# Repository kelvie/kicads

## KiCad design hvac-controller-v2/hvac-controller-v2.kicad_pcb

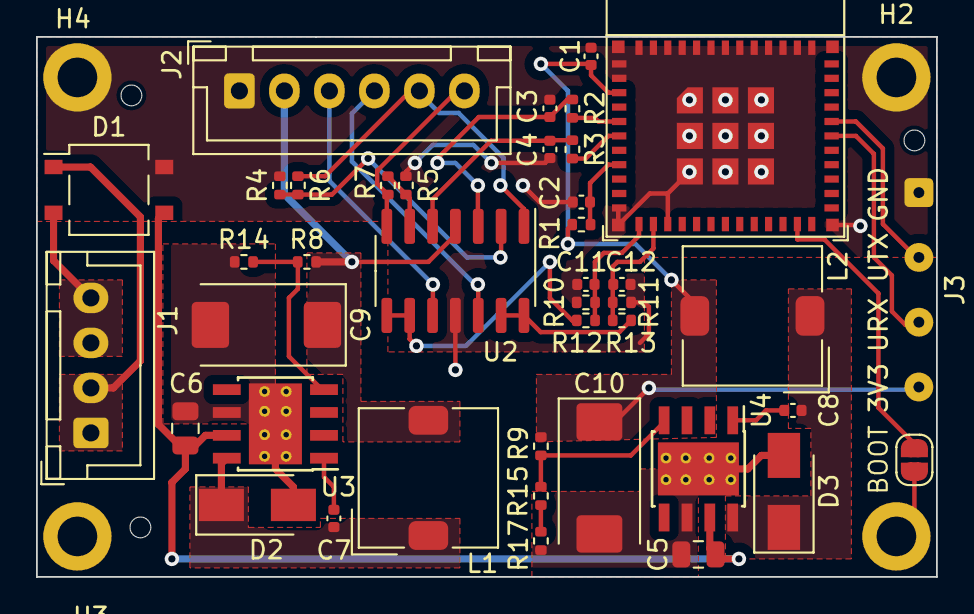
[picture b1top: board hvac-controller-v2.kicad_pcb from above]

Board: 2 copper layers, 50.0 x 30.0 mm, 48 parts (0 on the bottom side), 31 nets.

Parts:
C1: 0.01uF/16V; C_0402_1005Metric
C2, C3, C4: 1uF/5V; C_0402_1005Metric
C5, C6: 10uF/50V; C_0805_2012Metric
C7, C8: 0.01uF; C_0402_1005Metric
C9: 100uF/16V; CP_EIA-7343-31_Kemet-D
C10: 470uF/6.3V; CP_EIA-7343-31_Kemet-D
C11, C12: 0.1uF/16V; C_0402_1005Metric
D1: MB10S; TO-269AA
D2, D3: SS34; D_SMA
H1, H2, H3, H4: Hole; MountingHole_2.2mm_M2_DIN965_Pad
H5, H6, H7: ToolingHole; ToolingHole_1.152mm
J1: VAC IN; JST_XH_B4B-XH-A_1x04_P2.50mm_Vertical
J2: Conn_01x06; JST_XH_B6B-XH-A_1x06_P2.50mm_Vertical
J3: UART; SolderWire-0.1sqmm_1x04_P3.6mm_D0.4mm_OD1mm
JP1: BOOT; SolderJumper-2_P1.3mm_Open_RoundedPad1.0x1.5mm
L1, L2: 22uH; L_SXN_SMRH74-220MT
R1, R8, R9: 10k; R_0402_1005Metric
R2, R3, R14: 1.1k; R_0402_1005Metric
R4, R5: 33k; R_0402_1005Metric
R6, R7: 68k; R_0402_1005Metric
R10, R11: 18k; R_0402_1005Metric
R12, R13: 2k; R_0402_1005Metric
R15: 5.6k; R_0402_1005Metric
R17: 270; R_0402_1005Metric
U1: ESP32-C3-MINI-1
U2: LM324DT; SOIC-14_3.9x8.7mm_P1.27mm
U3, U4: TPS5430DDA; TI_SO-PowerPAD-8_ThermalVias

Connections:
+3V3: C1.1, C10.1, J3.4, L2.2, R1.1, R9.1, U1.3 (3V3)
+12V: C9.1, J2.2, L1.2, R8.1, U2.4 (V+)
+24VA: D1.2, J1.3, J1.4
-24VA: D1.1, J1.1, J1.2
/ADC1: C11.2, R10.2, R12.1, U1.12 (GPIO0/ADC1_CH0/XTAL_32K_P)
/ADC2: C12.2, R11.2, R13.1, U1.13 (GPIO1/ADC1_CH1/XTAL_32K_N)
/CTRL1_IN: J2.3, U2.10 (+)
/CTRL1_OUT: J2.5, R6.2, U2.1
/CTRL2_IN: J2.4, U2.12 (+)
/CTRL2_OUT: J2.6, R7.2, U2.7
/PH12: C7.2, D2.1 (K), L1.1, U3.8 (PH)
/PH33: C8.2, D3.1 (K), L2.1, U4.8 (PH)
/PWM1: R2.2, U1.5 (GPIO2/ADC1_CH2)
/PWM2: R3.2, U1.6 (GPIO3/ADC1_CH3)
/UART_RX: J3.3, U1.30 (GPIO20/U0RXD)
/UART_TX: J3.2, U1.31 (GPIO21/U0TXD)
GND: C1.2, C2.2, C3.2, C4.2, C5.2, C6.2, C9.2, C10.2, C11.1, C12.1, D1.4 (-), D2.2 (A), D3.2 (A), H1.1, H2.1, H3.1, H4.1, J2.1, J3.1, JP1.2 (B), R4.2, R5.2, R12.2, R13.2, R14.1, R17.1, U1.1 (GND), U1.2 (GND), U1.11 (GND), U1.14 (GND), U1.36 (GND), U2.11 (V-), U3.6 (GND), U3.9 (GNDPAD), U4.6 (GND), U4.9 (GNDPAD)
unnamed: C2.1, R1.2, U1.8 (EN/CHIP_PU)
unnamed: C3.1, R2.1, U2.3 (+)
unnamed: C4.1, R3.1, U2.5 (+)
unnamed: C5.1, C6.1, D1.3 (+), U3.7 (VIN), U4.7 (VIN)
unnamed: C7.1, U3.1 (BOOT)
unnamed: C8.1, U4.1 (BOOT)
unnamed: JP1.1 (A), U1.23 (GPIO9)
unnamed: R4.1, R6.1, U2.2 (-)
unnamed: R5.1, R7.1, U2.6 (-)
unnamed: R10.1, U2.8, U2.9 (-)
unnamed: R11.1, U2.13 (-), U2.14
unnamed: R8.2, R14.2, U3.4 (VSENSE)
unnamed: R15.1, R17.2
unnamed: R9.2, R15.2, U4.4 (VSENSE)

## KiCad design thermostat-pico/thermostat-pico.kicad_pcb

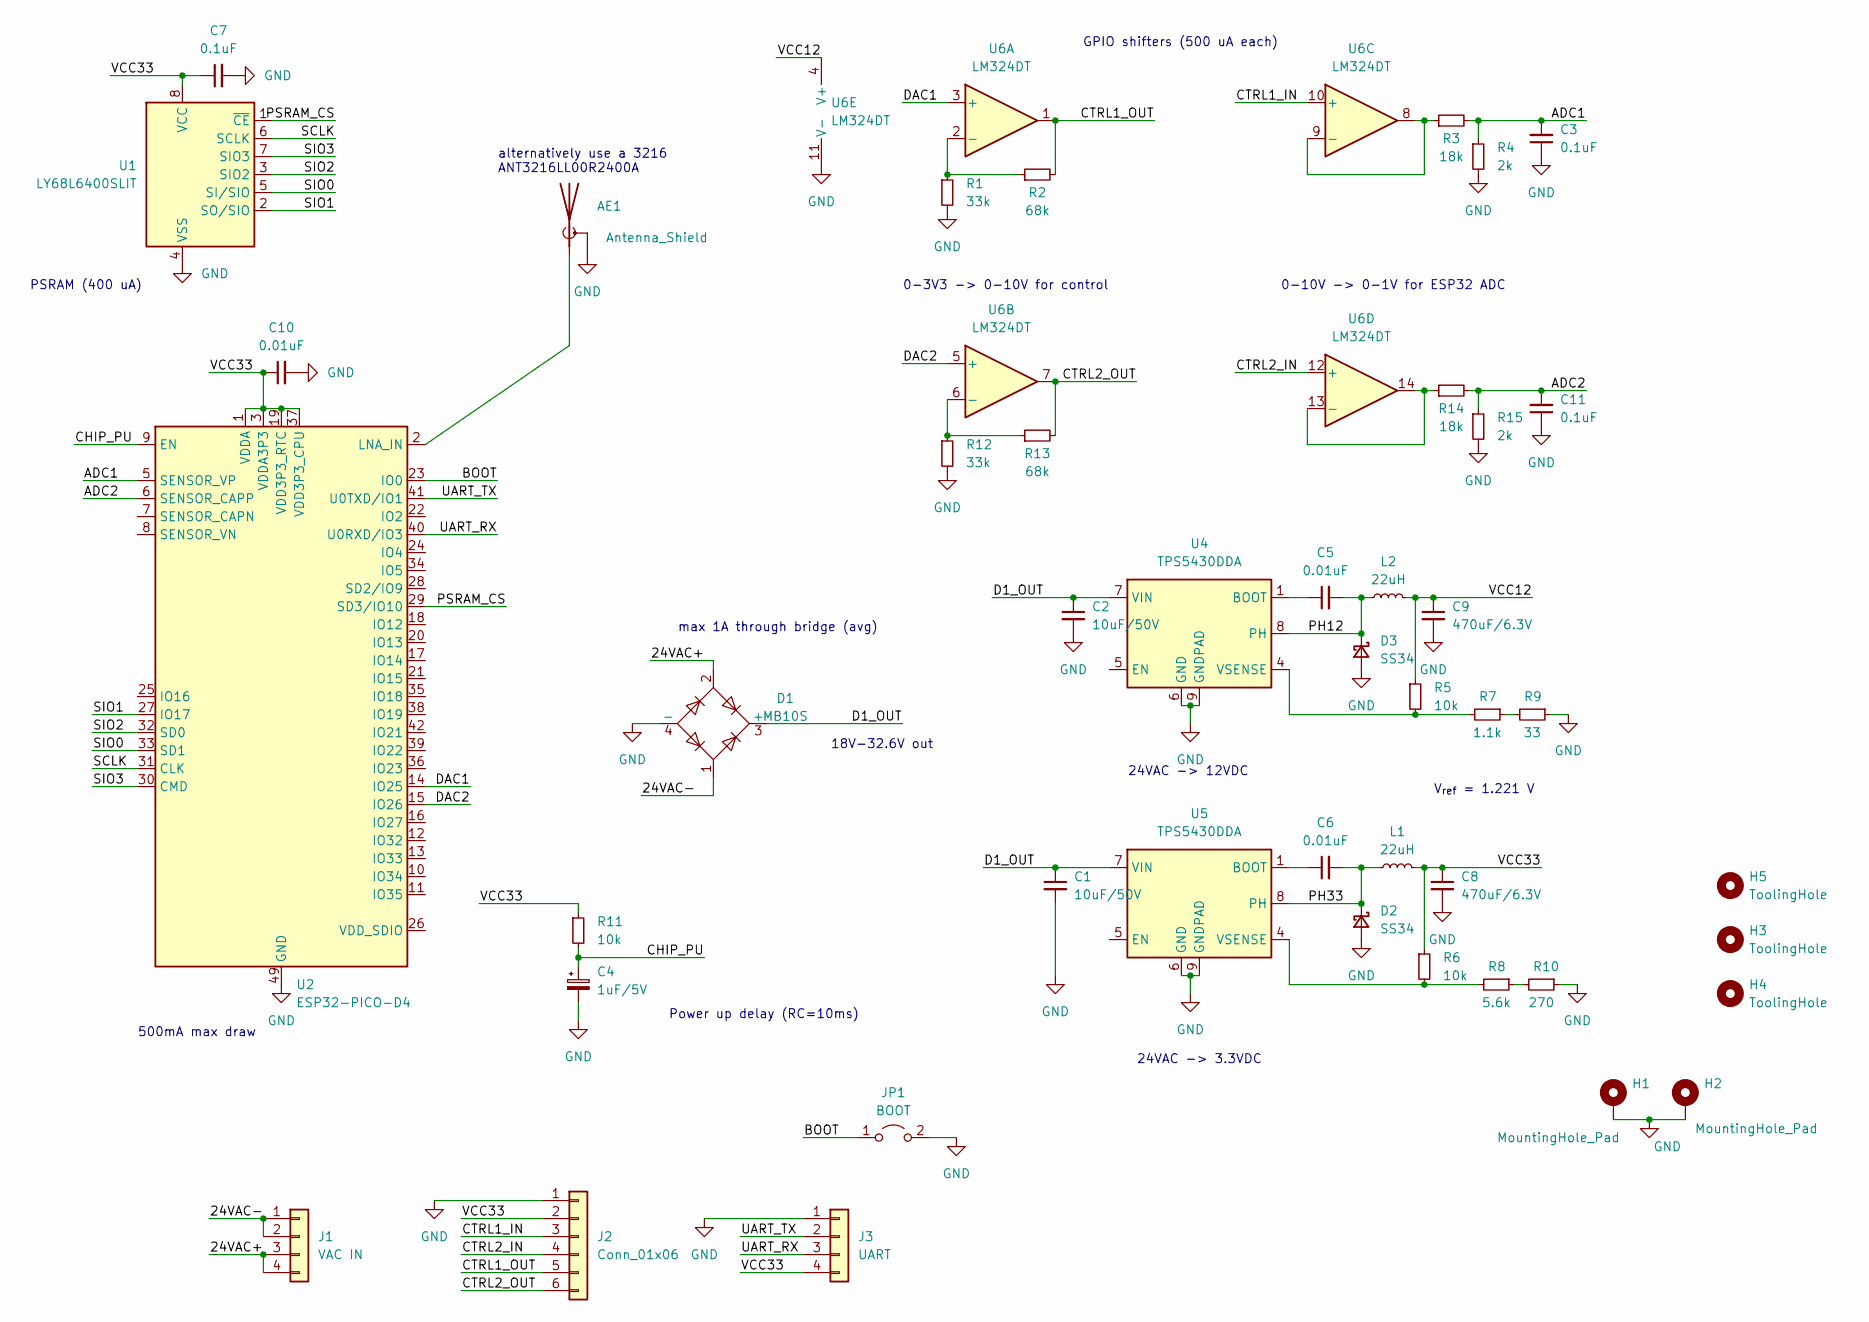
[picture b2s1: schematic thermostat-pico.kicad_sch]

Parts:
AE1: Antenna_Shield; Texas_SWRA117D_2.4GHz_Left
C1, C2: 10uF/50V; C_0805_2012Metric
C3, C7, C11: 0.1uF; C_0402_1005Metric
C4: 1uF/5V; C_0402_1005Metric
C5, C6, C10: 0.01uF; C_0402_1005Metric
C8, C9: 470uF/6.3V; CP_EIA-7343-31_Kemet-D
D1: MB10S; TO-269AA
D2, D3: SS34; D_SMA
H1, H2: MountingHole_Pad; MountingHole_2.2mm_M2_DIN965_Pad
H3, H4, H5: ToolingHole; ToolingHole_1.152mm
J1: VAC IN; JST_XH_B4B-XH-A_1x04_P2.50mm_Vertical
J2: Conn_01x06; JST_XH_B6B-XH-A_1x06_P2.50mm_Vertical
J3: UART; SolderWire-0.1sqmm_1x04_P3.6mm_D0.4mm_OD1mm
JP1: BOOT; SolderJumper-2_P1.3mm_Open_RoundedPad1.0x1.5mm
L1, L2: 22uH; L_SXN_SMRH74-220MT
R1, R12: 33k; R_0402_1005Metric
R2, R13: 68k; R_0402_1005Metric
R3, R14: 18k; R_0402_1005Metric
R4, R15: 2k; R_0402_1005Metric
R5, R6, R11: 10k; R_0402_1005Metric
R7: 1.1k; R_0402_1005Metric
R8: 5.6k; R_0402_1005Metric
R9: 33; R_0402_1005Metric
R10: 270; R_0402_1005Metric
U1: LY68L6400SLIT; SOIC-8_3.9x4.9mm_P1.27mm
U2: ESP32-PICO-D4; QFN-48-1EP_7x7mm_P0.5mm_EP5.3x5.3mm
U4, U5: TPS5430DDA; TI_SO-PowerPAD-8_ThermalVias
U6: LM324DT; SOIC-14_3.9x8.7mm_P1.27mm

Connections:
/24VAC+: D1.2, J1.3, J1.4
/24VAC-: D1.1, J1.1, J1.2
/ADC1: C3.2, R3.2, R4.1, U2.5 (SENSOR_VP)
/ADC2: C11.2, R14.2, R15.1, U2.6 (SENSOR_CAPP)
/BOOT: JP1.1 (A), U2.23 (IO0)
/CHIP_PU: C4.1, R11.2, U2.9 (EN)
/CTRL1_IN: J2.3, U6.10 (+)
/CTRL1_OUT: J2.5, R2.2, U6.1
/CTRL2_IN: J2.4, U6.12 (+)
/CTRL2_OUT: J2.6, R13.2, U6.7
/D1_OUT: C1.1, C2.1, D1.3 (+), U4.7 (VIN), U5.7 (VIN)
/DAC1: U2.14 (IO25), U6.3 (+)
/DAC2: U2.15 (IO26), U6.5 (+)
/PH12: C5.2, D3.1 (K), L2.1, U4.8 (PH)
/PH33: C6.2, D2.1 (K), L1.1, U5.8 (PH)
/PSRAM_CS: U1.1 (~CE), U2.29 (SD3/IO10)
/SCLK: U1.6 (SCLK), U2.31 (CLK)
/SIO0: U1.5 (SI/SIO), U2.33 (SD1)
/SIO1: U1.2 (SO/SIO), U2.27 (IO17)
/SIO2: U1.3 (SIO2), U2.32 (SD0)
/SIO3: U1.7 (SIO3), U2.30 (CMD)
/UART_RX: J3.3, U2.40 (U0RXD/IO3)
/UART_TX: J3.2, U2.41 (U0TXD/IO1)
GND: AE1.2 (Shield), C1.2, C2.2, C3.1, C4.2, C7.2, C8.2, C9.2, C10.2, C11.1, D1.4 (-), D2.2 (A), D3.2 (A), H1.1, H2.1, J2.1, J3.1, JP1.2 (B), R1.2, R4.2, R9.1, R10.1, R12.2, R15.2, U1.4 (VSS), U2.49 (GND), U4.6 (GND), U4.9 (GNDPAD), U5.6 (GND), U5.9 (GNDPAD), U6.11 (V-); also elsewhere on the board
unnamed: AE1.1 (A), U2.2 (LNA_IN)
unnamed: C5.1, U4.1 (BOOT)
unnamed: C6.1, U5.1 (BOOT)
unnamed: R1.1, R2.1, U6.2 (-)
unnamed: R3.1, U6.8, U6.9 (-)
unnamed: R7.1, R9.2
unnamed: R5.2, R7.2, U4.4 (VSENSE)
unnamed: R8.1, R10.2
unnamed: R6.2, R8.2, U5.4 (VSENSE)
unnamed: R12.1, R13.1, U6.6 (-)
unnamed: R14.1, U6.13 (-), U6.14

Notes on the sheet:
0-3V3 -> 0-10V for control
PSRAM (400 uA)
alternatively use a 3216 ANT3216LL00R2400A
24VAC -> 12VDC
500mA max draw
GPIO shifters (500 uA each)
18V-32.6V out
0-10V -> 0-1V for ESP32 ADC
24VAC -> 3.3VDC
V_{ref} = 1.221 V
max 1A through bridge (avg)
Power up delay (RC=10ms)

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
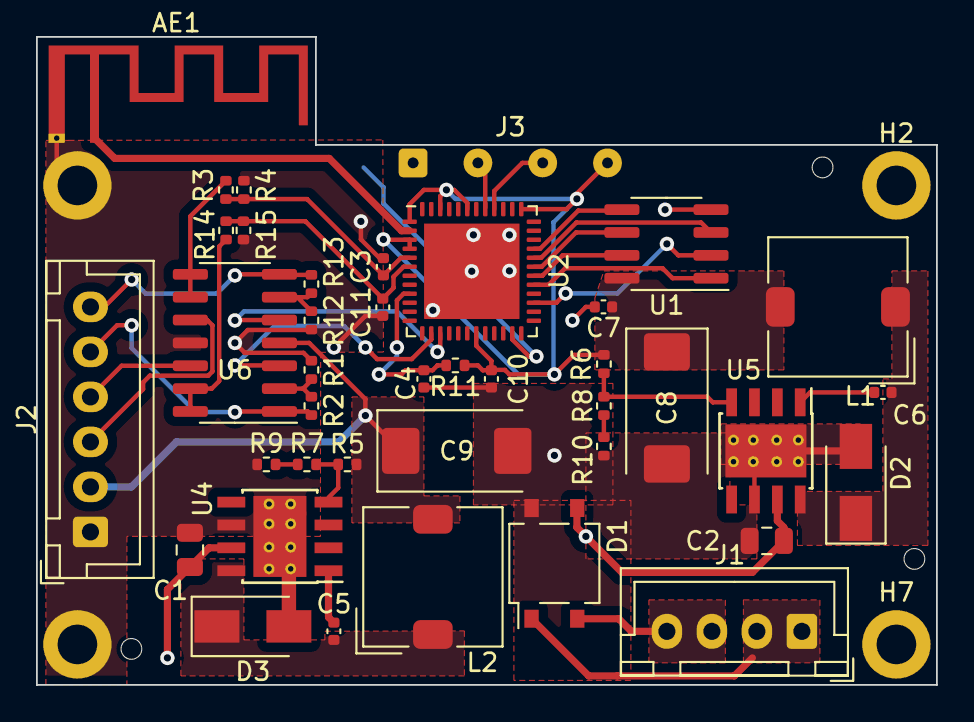
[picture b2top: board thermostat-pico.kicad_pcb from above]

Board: 2 copper layers, 50.0 x 36.0 mm, 48 parts (1 on the bottom side), 37 nets.

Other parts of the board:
H6, H7: Hole; MountingHole_2.2mm_M2_DIN965_Pad

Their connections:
GND: H6.1, H7.1; also elsewhere on the board

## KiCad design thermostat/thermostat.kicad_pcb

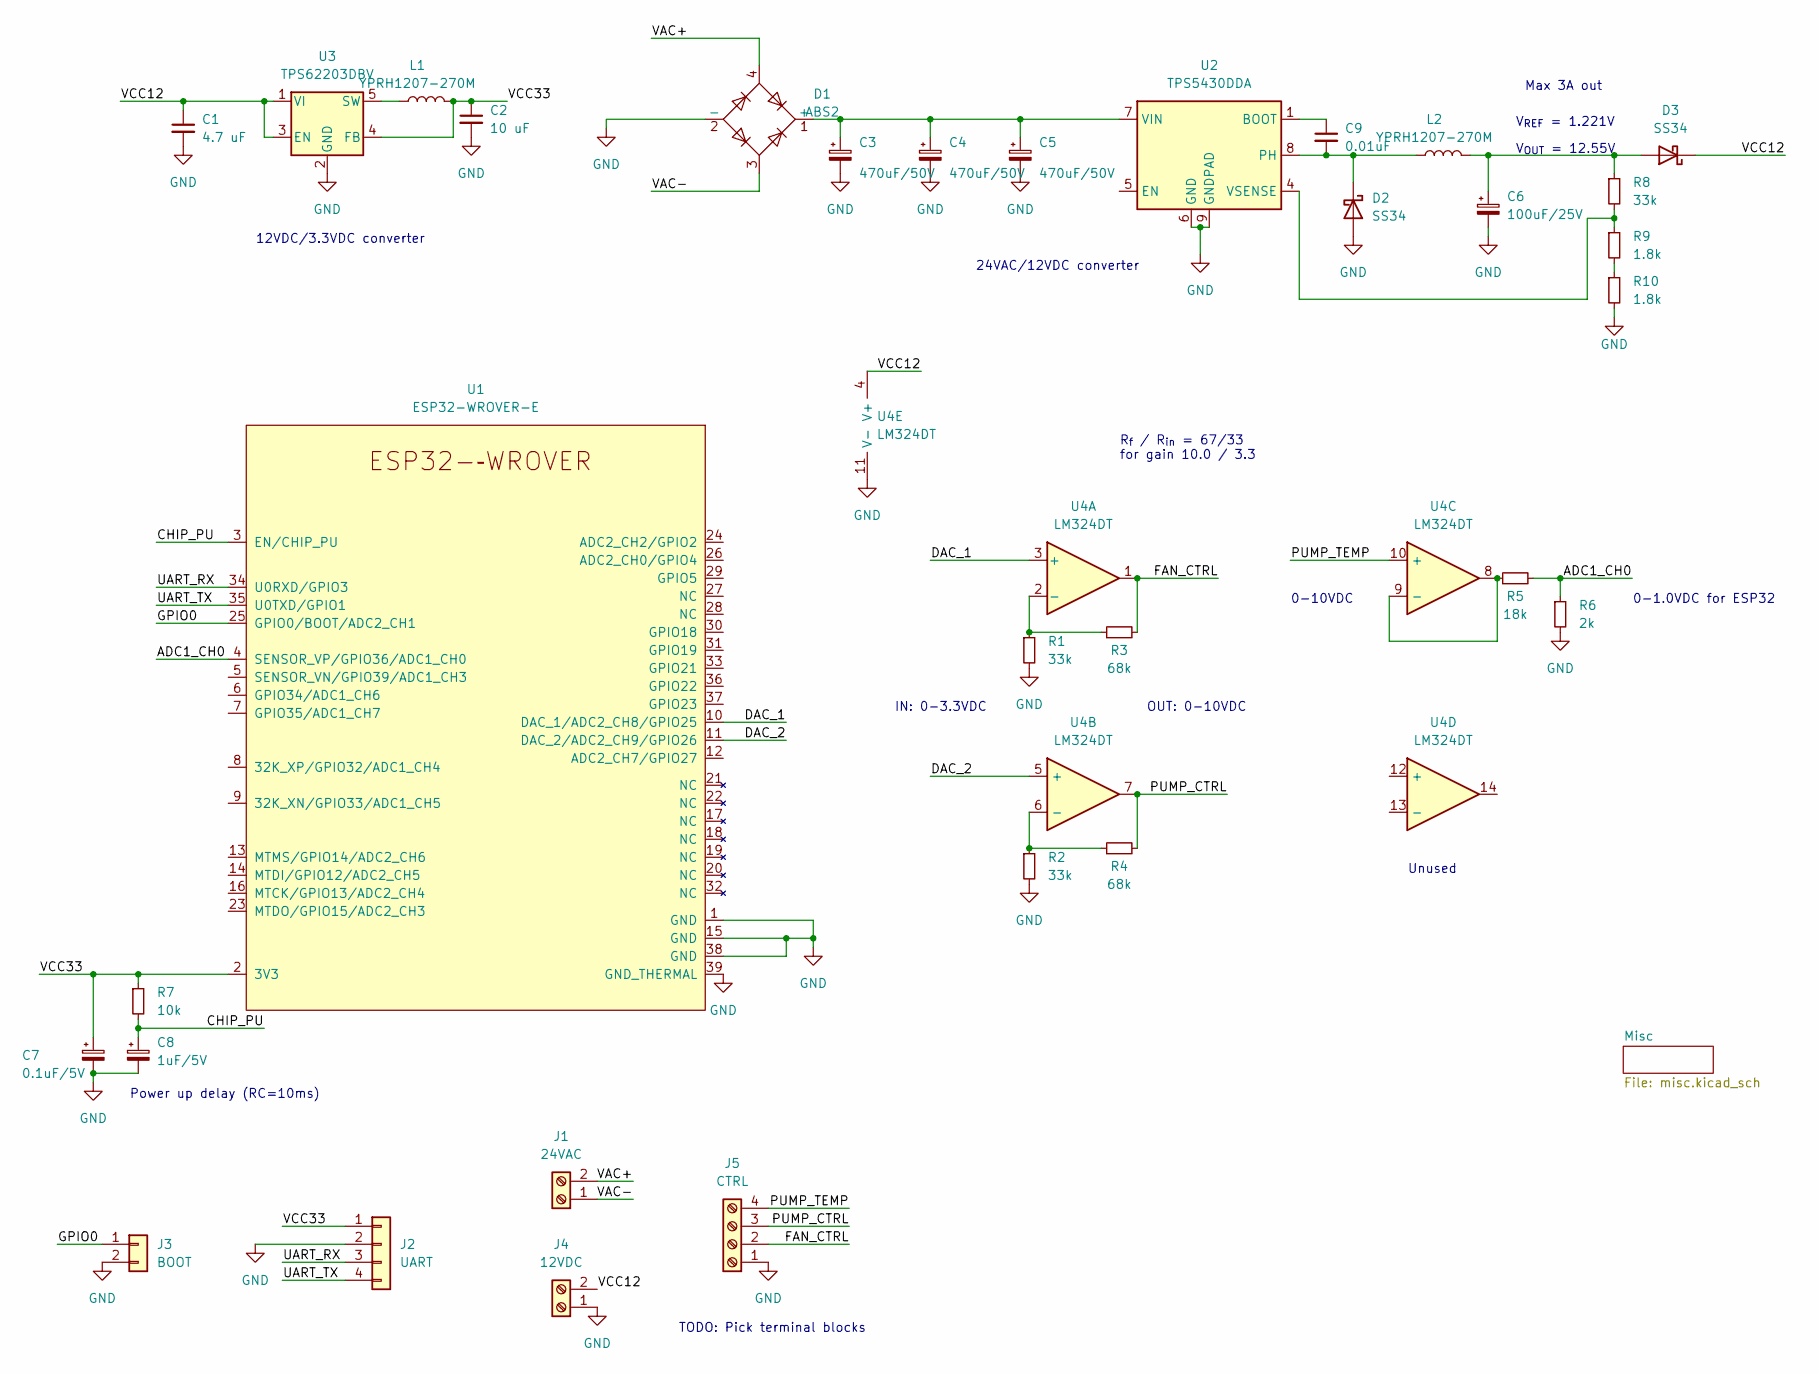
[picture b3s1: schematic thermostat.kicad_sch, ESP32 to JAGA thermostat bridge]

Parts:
C1: 4.7 uF; C_0805_2012Metric
C2: 10 uF; C_0805_2012Metric
C3, C4, C5: 470uF/50V; CP_Elec_6.3x7.7
C6: 100uF/25V; CP_Elec_6.3x7.7
C7: 0.1uF/5V; C_0201_0603Metric
C8: 1uF/5V; C_0402_1005Metric
C9: 0.01uF; C_0603_1608Metric
D1: ABS2; Diode_Bridge_Diotec_ABS
D2, D3: SS34; D_SOD-128
J1: 24VAC; TerminalBlock_RND_205-00001_1x02_P5.00mm_Horizontal
J2: UART; PinHeader_1x04_P2.54mm_Horizontal
J3: BOOT; PinHeader_1x02_P2.54mm_Horizontal
J4: 12VDC; TerminalBlock_RND_205-00001_1x02_P5.00mm_Horizontal
J5: CTRL; TerminalBlock_RND_205-00003_1x04_P5.00mm_Horizontal
L1, L2: YPRH1207-270M; L_12x12mm_H8mm
R1, R2, R8: 33k; R_0201_0603Metric
R3, R4: 68k; R_0201_0603Metric
R5: 18k; R_0201_0603Metric
R6: 2k; R_0201_0603Metric
R7: 10k; R_0201_0603Metric
R9, R10: 1.8k; R_0201_0603Metric
U1: ESP32-WROVER-E
U2: TPS5430DDA; TI_SO-PowerPAD-8_ThermalVias
U3: TPS62203DBV; SOT-23-5
U4: LM324DT; SOIC-14_3.9x8.7mm_P1.27mm

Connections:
/ADC1_CH0: R5.2, R6.1, U1.4 (SENSOR_VP/GPIO36/ADC1_CH0)
/CHIP_PU: C8.1, R7.2, U1.3 (EN/CHIP_PU)
/DAC_1: U1.10 (DAC_1/ADC2_CH8/GPIO25), U4.3 (+)
/DAC_2: U1.11 (DAC_2/ADC2_CH9/GPIO26), U4.5 (+)
/FAN_CTRL: J5.2, R3.2, U4.1
/GPIO0: J3.1, U1.25 (GPIO0/BOOT/ADC2_CH1)
/PUMP_CTRL: J5.3, R4.2, U4.7
/PUMP_TEMP: J5.4, U4.10 (+)
/UART_RX: J2.3, U1.34 (U0RXD/GPIO3)
/UART_TX: J2.4, U1.35 (U0TXD/GPIO1)
/VAC+: D1.4, J1.2
/VAC-: D1.3, J1.1
/VCC12: C1.1, D3.1 (K), J4.2, U3.1 (VI), U3.3 (EN), U4.4 (V+)
/VCC33: C2.1, C7.1, J2.1, L1.2, R7.1, U1.2 (3V3), U3.4 (FB)
GND: C1.2, C2.2, C3.2, C4.2, C5.2, C6.2, C7.2, C8.2, D1.2 (-), D2.2 (A), J2.2, J3.2, J4.1, J5.1, R1.2, R2.2, R6.2, R10.2, U1.1 (GND), U1.15 (GND), U1.38 (GND), U1.39 (GND_THERMAL), U2.6 (GND), U2.9 (GNDPAD), U3.2 (GND), U4.11 (V-); also elsewhere on the board
unnamed: C3.1, C4.1, C5.1, D1.1 (+), U2.7 (VIN)
unnamed: C6.1, D3.2 (A), L2.2, R8.1
unnamed: C9.1, U2.1 (BOOT)
unnamed: C9.2, D2.1 (K), L2.1, U2.8 (PH)
unnamed: L1.1, U3.5 (SW)
unnamed: R1.1, R3.1, U4.2 (-)
unnamed: R2.1, R4.1, U4.6 (-)
unnamed: R5.1, U4.8, U4.9 (-)
unnamed: R8.2, R9.1, U2.4 (VSENSE)
unnamed: R9.2, R10.1

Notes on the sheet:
Unused
Power up delay (RC=10ms)
OUT: 0-10VDC
V_{REF} = 1.221V
TODO: Pick terminal blocks
R_{f} / R_{in} = 67/33 for gain 10.0 / 3.3
Max 3A out
0-1.0VDC for ESP32
IN: 0-3.3VDC
24VAC/12VDC converter
V_{OUT} = 12.55V
0-10VDC
12VDC/3.3VDC converter

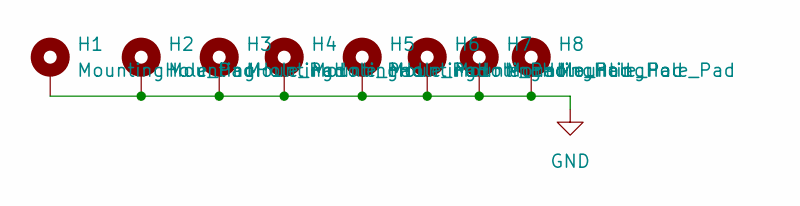
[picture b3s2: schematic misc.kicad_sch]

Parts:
H1, H2: MountingHole_Pad; MountingHole_No6_Pad_TopBottom
H3, H4, H5, H6, H7, H8: MountingHole_Pad; MountingHole_2.2mm_M2_DIN965_Pad_TopBottom

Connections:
GND: H1.1, H2.1, H3.1, H4.1, H5.1, H6.1, H7.1, H8.1; also elsewhere on the board

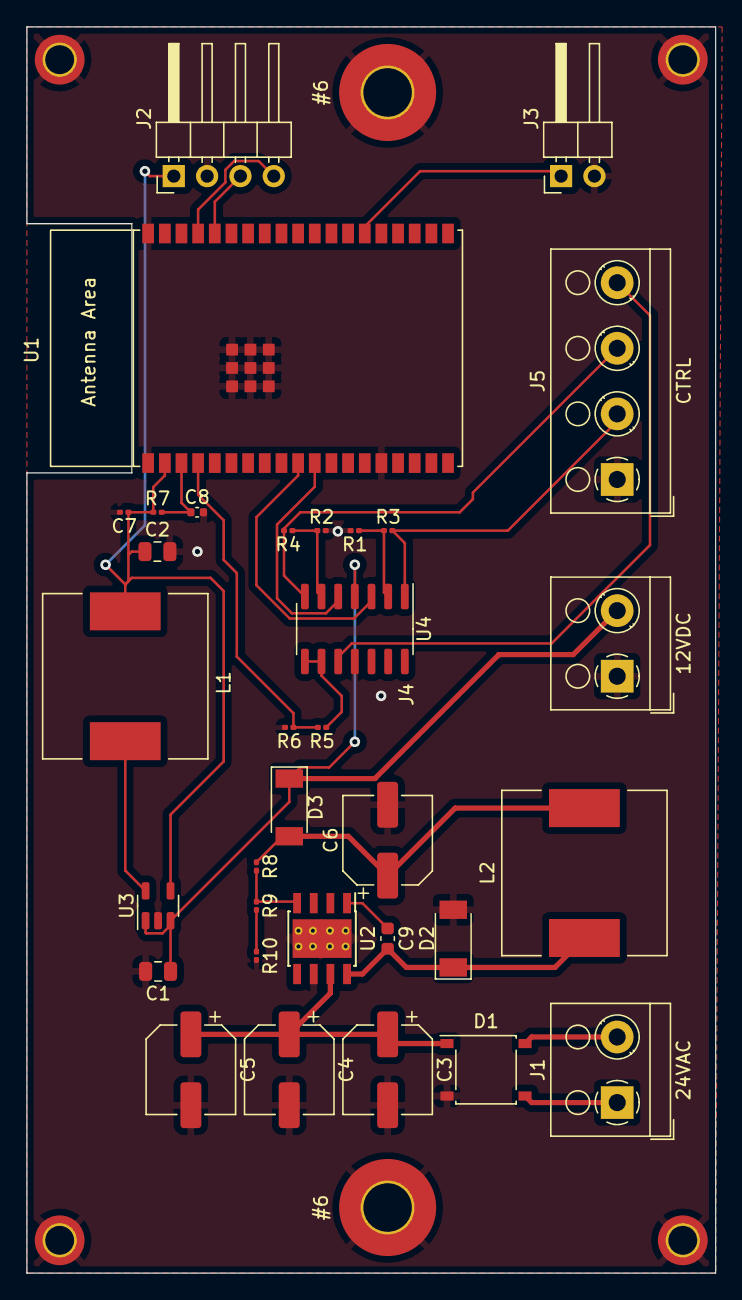
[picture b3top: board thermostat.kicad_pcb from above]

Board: 2 copper layers, 52.5 x 95.0 mm, 39 parts (0 on the bottom side), 25 nets.

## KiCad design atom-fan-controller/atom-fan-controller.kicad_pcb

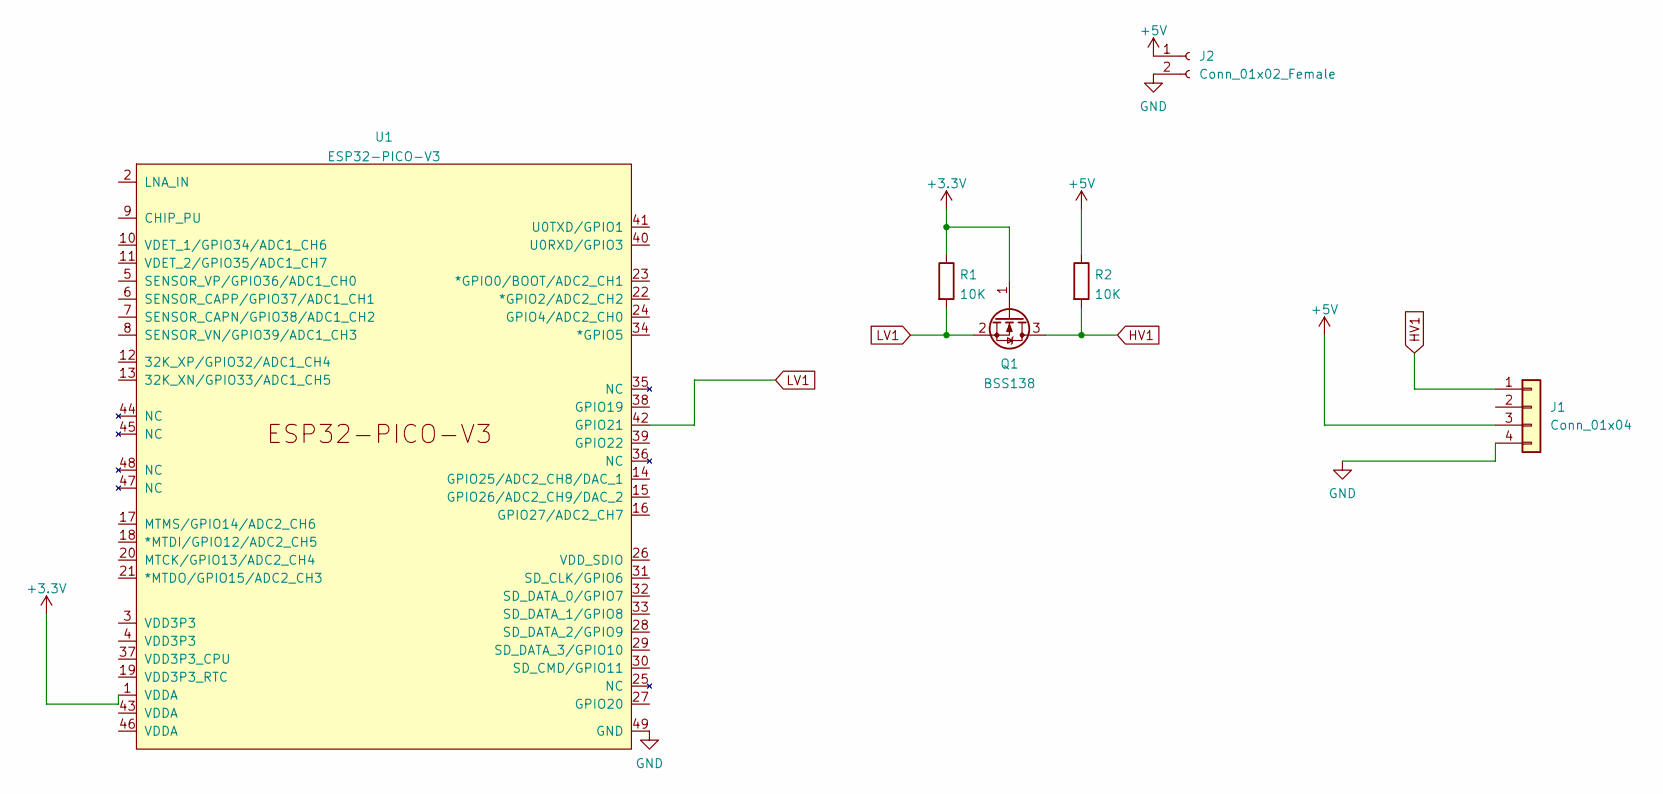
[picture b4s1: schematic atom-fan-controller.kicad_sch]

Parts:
J1: Conn_01x04; FanPinHeader_1x04_P2.54mm_Vertical
J2: Conn_01x02_Female; Molex_KK-254_AE-6410-02A_1x02_P2.54mm_Vertical
Q1: BSS138; SOT-23
R1, R2: 10K; R_0201_0603Metric
U1: ESP32-PICO-V3; QFN-48-1EP_7x7mm_P0.5mm_EP5.15x5.15mm

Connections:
+3V3: Q1.1 (G), R1.1, U1.1 (VDDA)
+5V: J1.3 (VCC), J2.1, R2.1
GND: J1.4 (GND), J2.2, U1.49 (GND)
HV1: J1.1 (PWM), Q1.3 (D), R2.2
LV1: Q1.2 (S), R1.2, U1.42 (GPIO21)

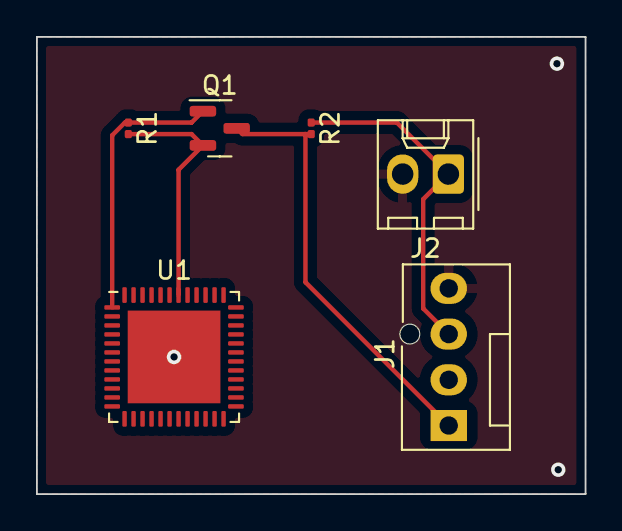
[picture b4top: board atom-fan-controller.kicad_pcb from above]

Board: 2 copper layers, 30.5 x 25.4 mm, 6 parts (0 on the bottom side), 5 nets.

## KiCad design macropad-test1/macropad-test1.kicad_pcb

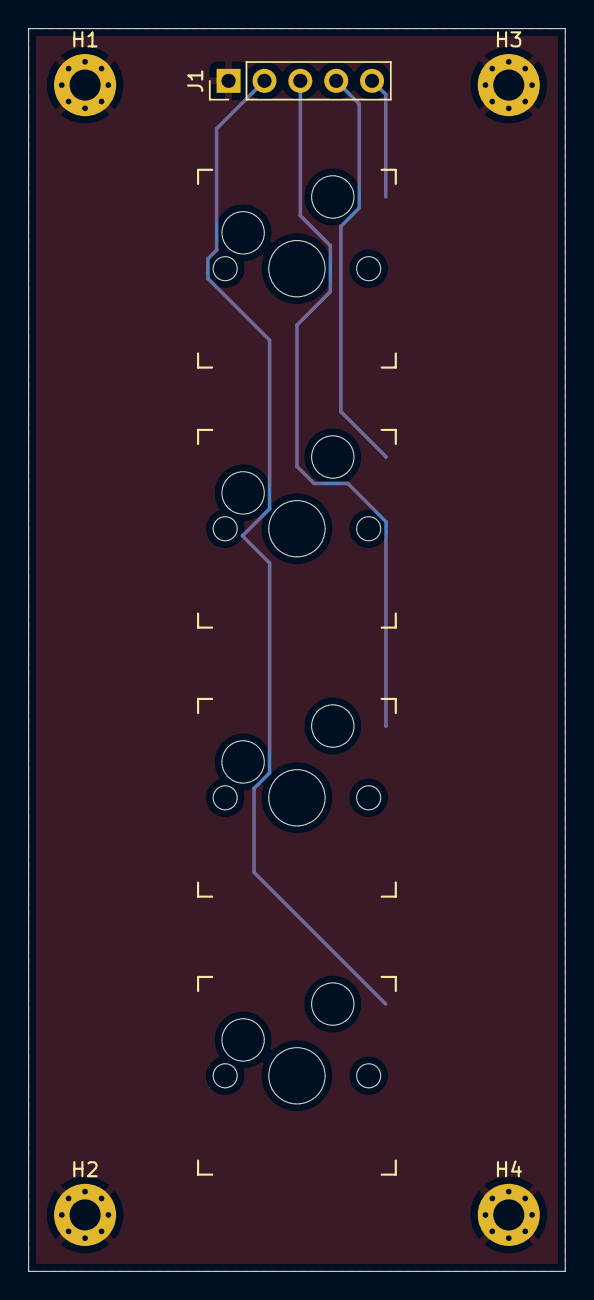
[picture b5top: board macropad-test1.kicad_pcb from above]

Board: 2 copper layers, 38.0 x 88.0 mm, 9 parts (0 on the bottom side), 5 nets.

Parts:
H1, H2, H3, H4: MountingHole_Pad; MountingHole_2.2mm_M2_Pad_Via
J1: Conn_01x05_Female; PinHeader_1x05_P2.54mm_Vertical
SW1, SW2, SW3, SW4: SW_Push; Kailh_socket_MX

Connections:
GND: H1.1, H2.1, H3.1, H4.1, J1.1, SW1.2, SW2.2, SW3.2, SW4.2
unnamed: J1.2, SW4.1
unnamed: J1.3, SW3.1
unnamed: J1.4, SW2.1
unnamed: J1.5, SW1.1

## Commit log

2022-05-26 update thermostat
    I think I chose all the parts, just need to optimize the layout
2022-05-27 layout with holes to fit in old slot
2022-05-27 Better layout with shorter debug pins
2022-05-28 simpler smaller thermostat (wip)
2022-06-01 Should be finished
    Maybe the antenna could be different
2022-06-01 Added slow start circuit
2022-06-05 Add more connectors
    And use a bigger op-amp. Surprised this fit.
2022-06-05 Assembly updates
    Apparently they can't do 0201 and need tooling holes
2022-06-05 Update schematic as well
2022-06-05 Update tracks, add inductor 3D model
2022-06-06 Add review files
    And a few dependencies
2022-06-06 Start v2 of hvac-controller
    thermostat doesn't make sense as it doesn't have a temp sensor.
2022-06-07 Laid out board, sans boot jumper
    Trying to figure out if I can hook this up to serial somehow.
2022-06-07 Silkscreen clean up.
    I think I want to move the antenna to the top edge though
2022-06-11 Re-layout schematic and PCB
    I wanted the antenna on top (long edge).
2022-06-11 Add schematic PDF
2022-06-12 Update hvac controller with better clearances
2022-06-12 Start v3, with an external m5stamp
2022-06-15 Add v2.1 and v3
    To try to make it smaller
2022-06-16 checkpoint
